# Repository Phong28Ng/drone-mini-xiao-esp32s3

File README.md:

# Drone mini XIAO ESP32-S3

Đồ án môn học của nhóm: drone mini 4 cánh dùng XIAO ESP32-S3, điều khiển bằng app ESP-Drone trên điện thoại qua Wi-Fi.

Drone đã bay thử được, giữ cân bằng khá ổn. Hiện tại con XIAO ESP32-S3 bị hỏng lúc tháo bo ra khỏi khung, nhóm đang chờ mạch mới về để lắp lại.

## Thư mục

- `firmware/` – code ESP-Drone, đã chỉnh chân cho bo của nhóm
- `hardware/` – file KiCad, Gerber, BOM, sơ đồ nguyên lý
- `frame/` – khung 3D
- `docs/` – sơ đồ khối, lưu đồ, ảnh app và ảnh drone

## Phần cứng

- XIAO ESP32-S3
- Cảm biến MPU-6050
- 4 motor coreless 6x15mm, mỗi motor 1 MOSFET KSI2300DS
- Pin LiPo 1S 3.7V
- PCB 4 lớp 17.75 x 21mm, làm lại từ thiết kế ESP-FLY rồi đặt xưởng gia công
- Khung tự vẽ trên SolidWorks rồi đem in 3D

Chân đang dùng:

| Chức năng | GPIO |
|---|---|
| Motor M1 (trước phải) | 7 |
| Motor M2 (sau phải) | 4 |
| Motor M3 (sau trái) | 3 |
| Motor M4 (trước trái) | 1 |
| SDA / SCL (MPU-6050) | 5 / 6 |
| INT (MPU-6050) | 8 |
| Đo điện áp pin | 2 |
| LED đỏ / LED xanh lá | 43 / 9 |

## Build và nạp code

Nhóm dùng ESP-IDF 5.0.

```
cd firmware
idf.py build
idf.py -p COMx flash monitor
```

Không chạy `idf.py set-target` vì nó sẽ tạo lại `sdkconfig` và mất cấu hình chân.

So với code gốc, nhóm sửa `sdkconfig` (chân motor, I2C, LED) và `motors.h` (cho motor quay thử lâu hơn lúc khởi động để dễ quan sát).

## Cách điều khiển

1. Cắm pin, đợi 4 motor quay thử lần lượt và LED xanh chớp 5 lần.
2. Điện thoại vào Wi-Fi `ESP-DRONE_xxxx`, mật khẩu `12345678`.
3. Mở app ESP-Drone, bấm kết nối, kéo ga về 0 trước rồi mới đẩy ga lên.

## Thành viên

- Ngô Hải Nam (nhóm trưởng) – thiết kế PCB, hàn mạch
- Phạm Chu Quốc – thiết kế và in khung 3D, cài app
- Nguyễn Hữu Phong – báo cáo, lưu đồ, tìm hiểu PID

GVHD: TS. Đỗ Trần Thắng – Trường Đại học Công nghệ, ĐHQGHN

## Tham khảo

- Firmware: [espressif/esp-drone](https://github.com/espressif/esp-drone)
- Mạch: [ESP-FLY](https://github.com/Seeed-Projects/Co-Create_ESP-FLY) của Max Imagination

Giấy phép GPL-3.0 theo dự án gốc.

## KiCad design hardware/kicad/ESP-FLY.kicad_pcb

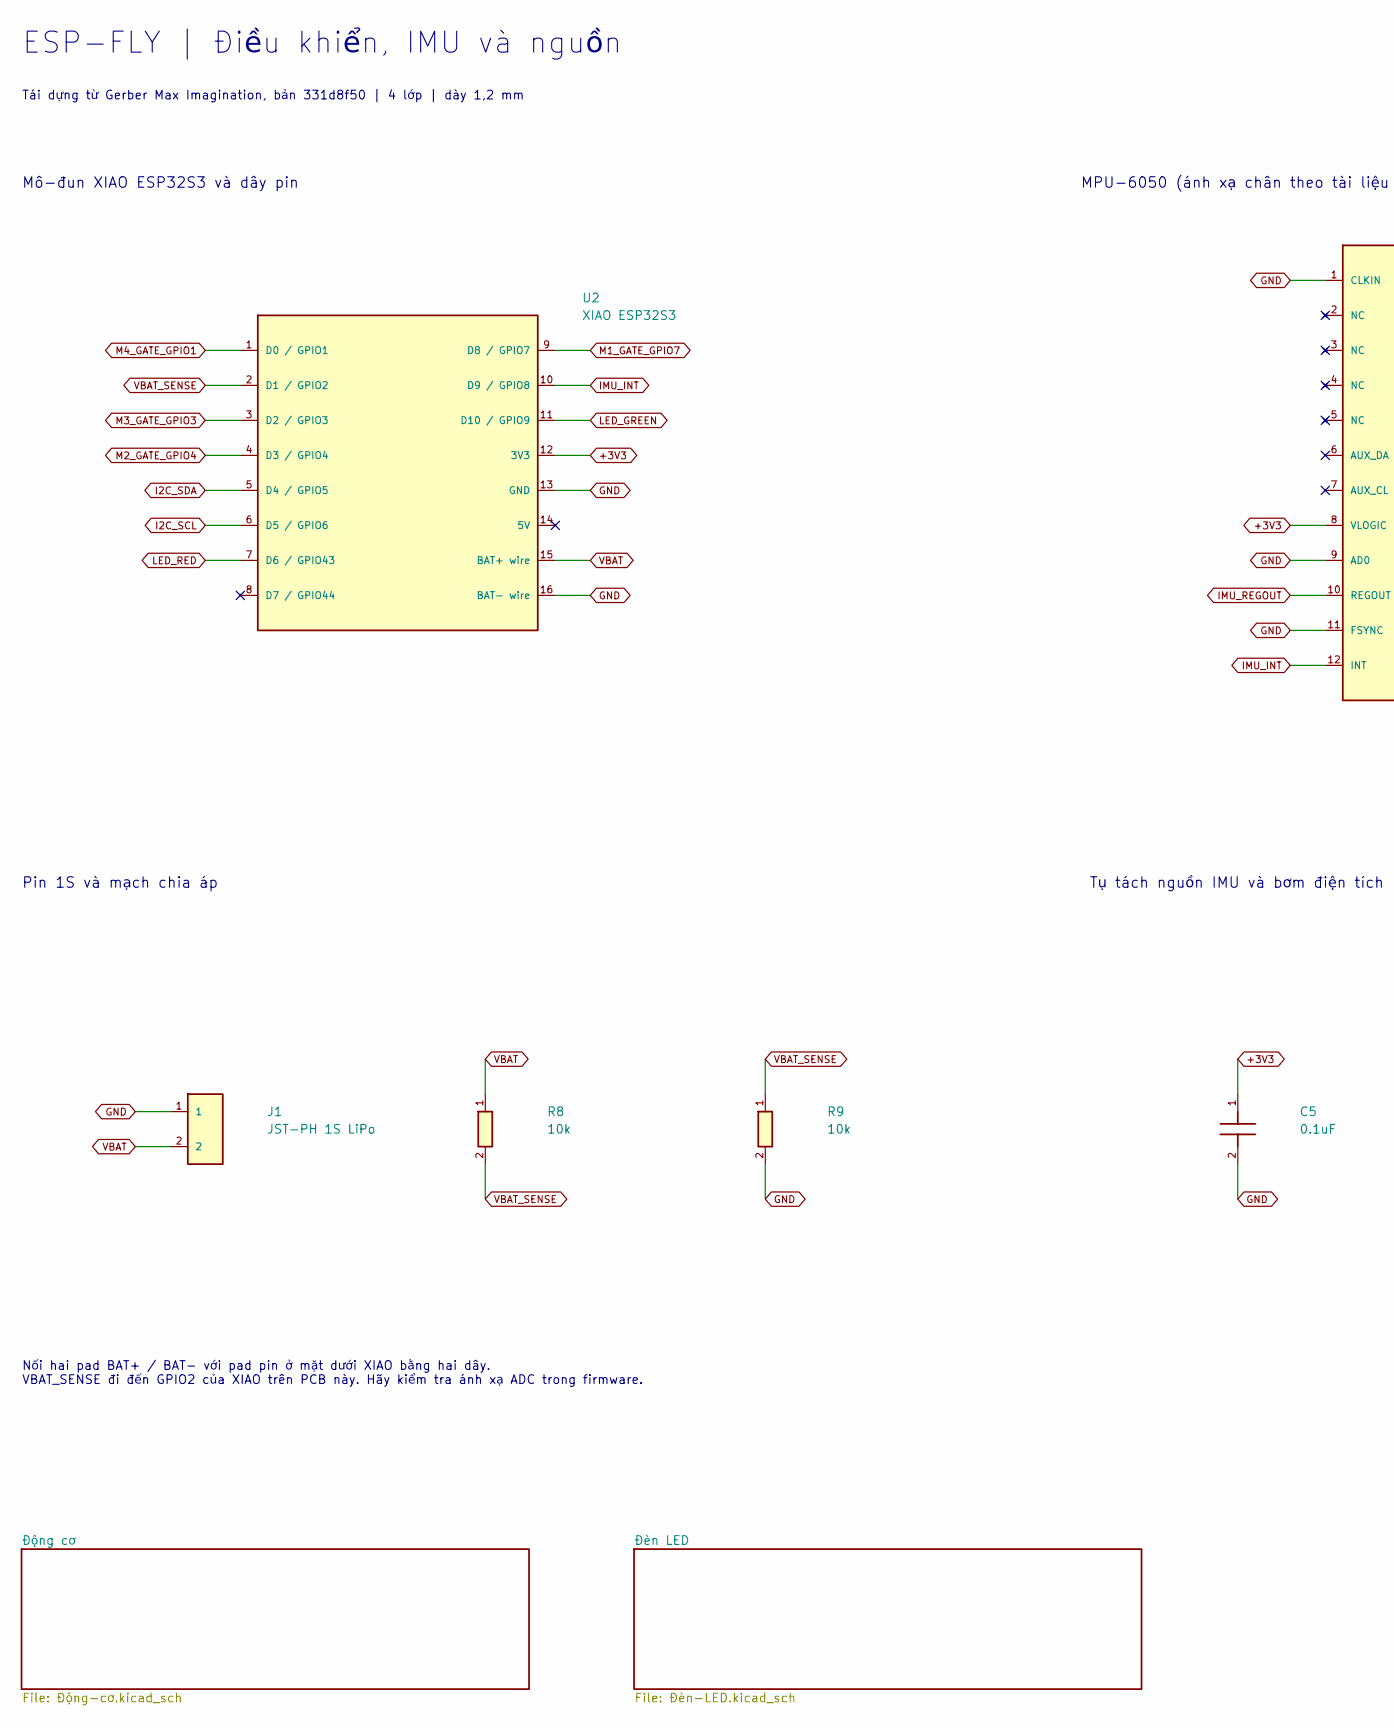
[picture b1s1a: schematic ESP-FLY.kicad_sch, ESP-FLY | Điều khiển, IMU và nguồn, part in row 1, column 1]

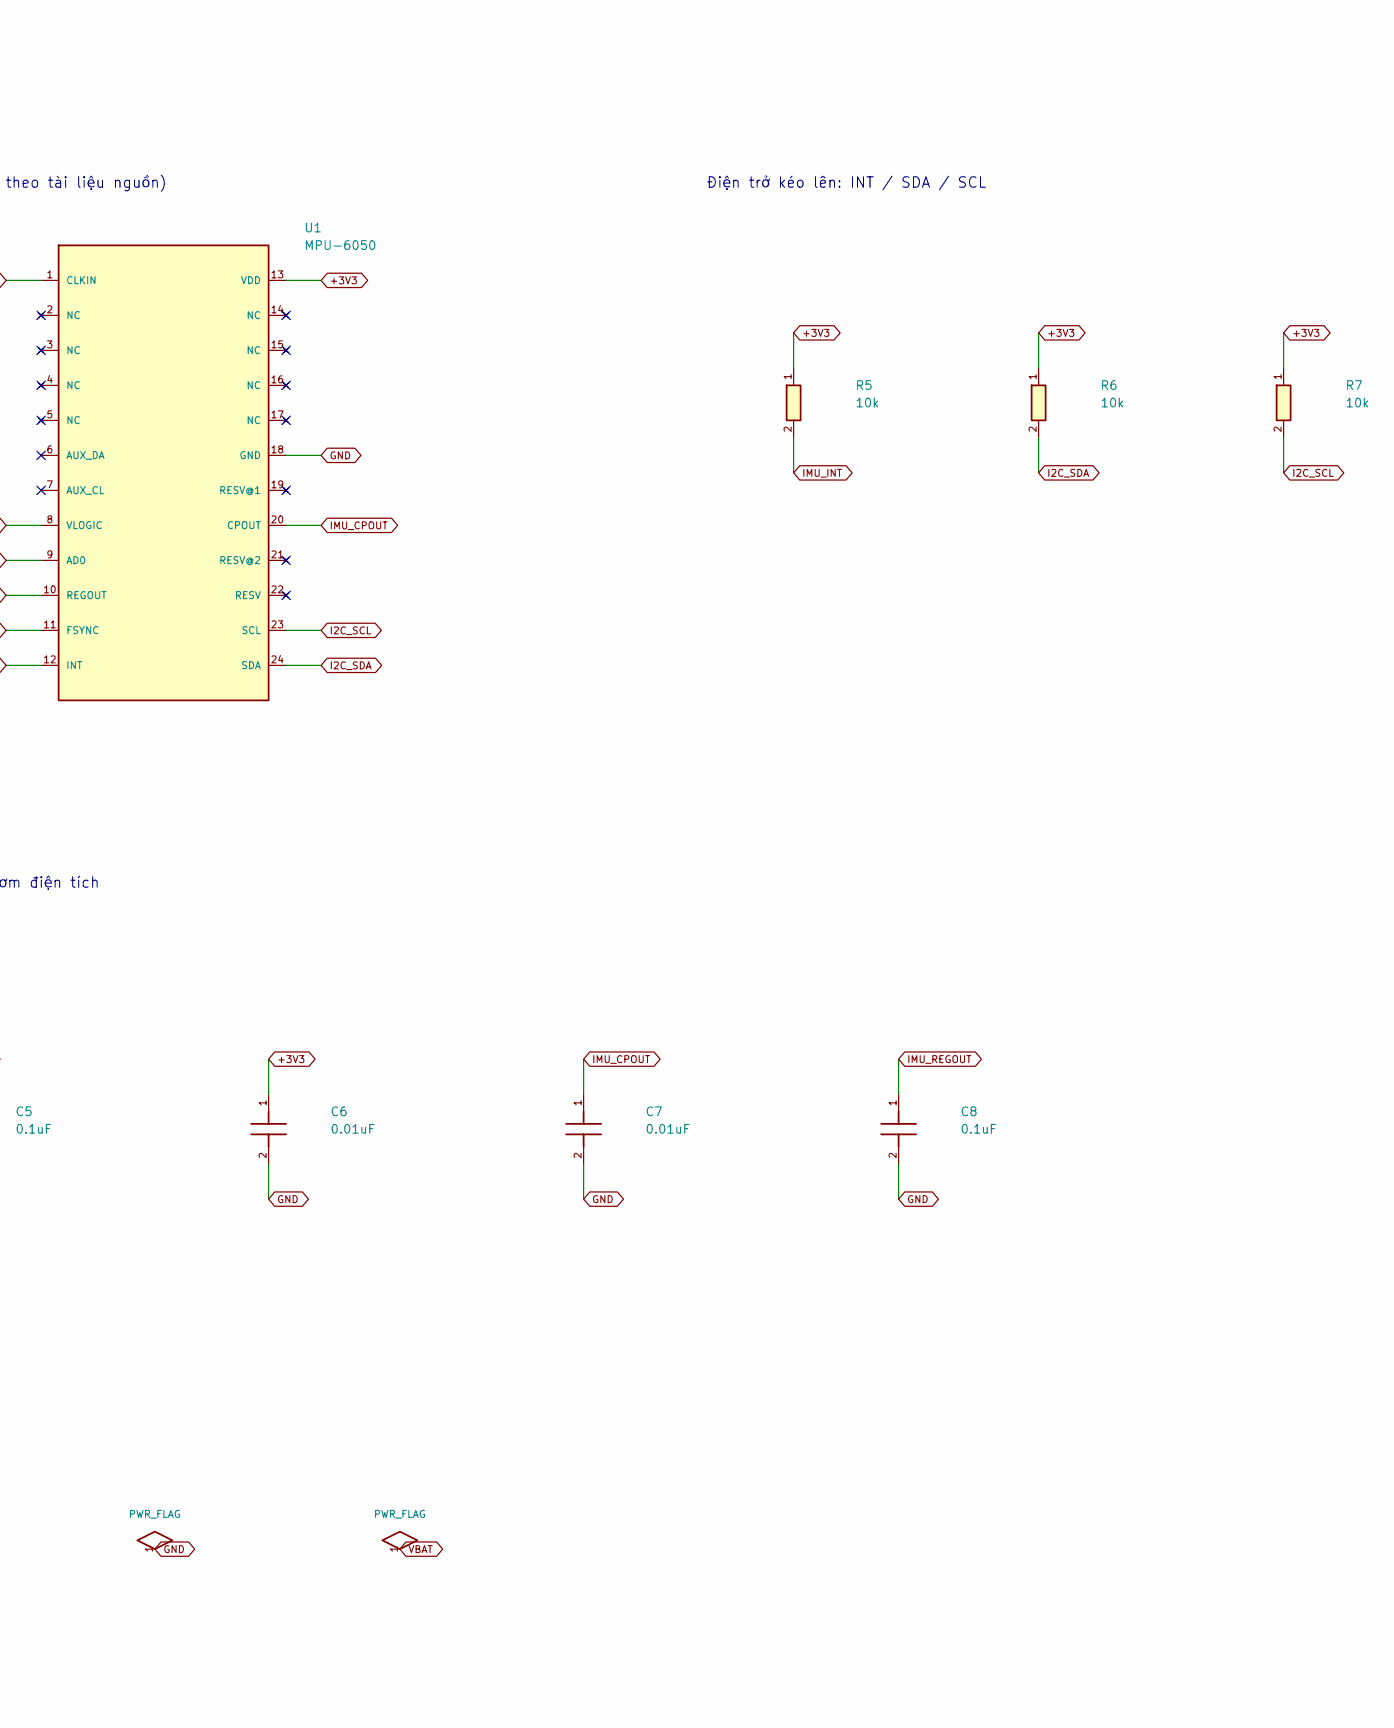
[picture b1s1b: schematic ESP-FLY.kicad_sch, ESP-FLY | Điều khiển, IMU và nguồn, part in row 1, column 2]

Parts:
C5: 0.1uF; C5; ManufacturerPartNumber CL21B104KBCNNNC
C6: 0.01uF; C6; ManufacturerPartNumber CC0805KRX7R9BB103
C7: 0.01uF; C7; ManufacturerPartNumber CC0805KRX7R9BB103
C8: 0.1uF; C8; ManufacturerPartNumber CL21B104KBCNNNC
J1: JST-PH 1S LiPo; J1; ManufacturerPartNumber S2B-PH-K-S(LF)(SN)
R5: 10k; R5; ManufacturerPartNumber FRC0805F1002TS
R6: 10k; R6; ManufacturerPartNumber FRC0805F1002TS
R7: 10k; R7; ManufacturerPartNumber FRC0805F1002TS
R8: 10k; R8; ManufacturerPartNumber FRC0805F1002TS
R9: 10k; R9; ManufacturerPartNumber FRC0805F1002TS
U1: MPU-6050; U1; ManufacturerPartNumber MPU-6050
U2: XIAO ESP32S3; U2

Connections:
+3V3: C5.1, C6.1, R5.1, R6.1, R7.1, U1.8 (VLOGIC), U1.13 (VDD), U2.12 (3V3); also elsewhere on the board
GND: C5.2, C6.2, C7.2, C8.2, J1.1, R9.2, U1.1 (CLKIN), U1.9 (AD0), U1.11 (FSYNC), U1.18 (GND), U2.13 (GND), U2.16 (BAT- wire); also elsewhere on the board
I2C_SCL: R7.2, U1.23 (SCL), U2.6 (D5 / GPIO6)
I2C_SDA: R6.2, U1.24 (SDA), U2.5 (D4 / GPIO5)
IMU_CPOUT: C7.1, U1.20 (CPOUT)
IMU_INT: R5.2, U1.12 (INT), U2.10 (D9 / GPIO8)
IMU_REGOUT: C8.1, U1.10 (REGOUT)
LED_GREEN: U2.11 (D10 / GPIO9); also elsewhere on the board
LED_RED: U2.7 (D6 / GPIO43); also elsewhere on the board
M1_GATE_GPIO7: U2.9 (D8 / GPIO7); also elsewhere on the board
M2_GATE_GPIO4: U2.4 (D3 / GPIO4); also elsewhere on the board
M3_GATE_GPIO3: U2.3 (D2 / GPIO3); also elsewhere on the board
M4_GATE_GPIO1: U2.1 (D0 / GPIO1); also elsewhere on the board
VBAT: J1.2, R8.1, U2.15 (BAT+ wire); also elsewhere on the board
VBAT_SENSE: R8.2, R9.1, U2.2 (D1 / GPIO2)

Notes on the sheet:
ESP-FLY | Điều khiển, IMU và nguồn
Tái dựng từ Gerber Max Imagination, bản 331d8f50 | 4 lớp | dày 1,2 mm
Mô-đun XIAO ESP32S3 và dây pin
MPU-6050 (ánh xạ chân theo tài liệu nguồn)
Điện trở kéo lên: INT / SDA / SCL
Pin 1S và mạch chia áp
Tụ tách nguồn IMU và bơm điện tích
Nối hai pad BAT+ / BAT- với pad pin ở mặt dưới XIAO bằng hai dây. VBAT_SENSE đi đến GPIO2 của XIAO trên PCB này. Hãy kiểm tra ánh xạ ADC trong firmware.

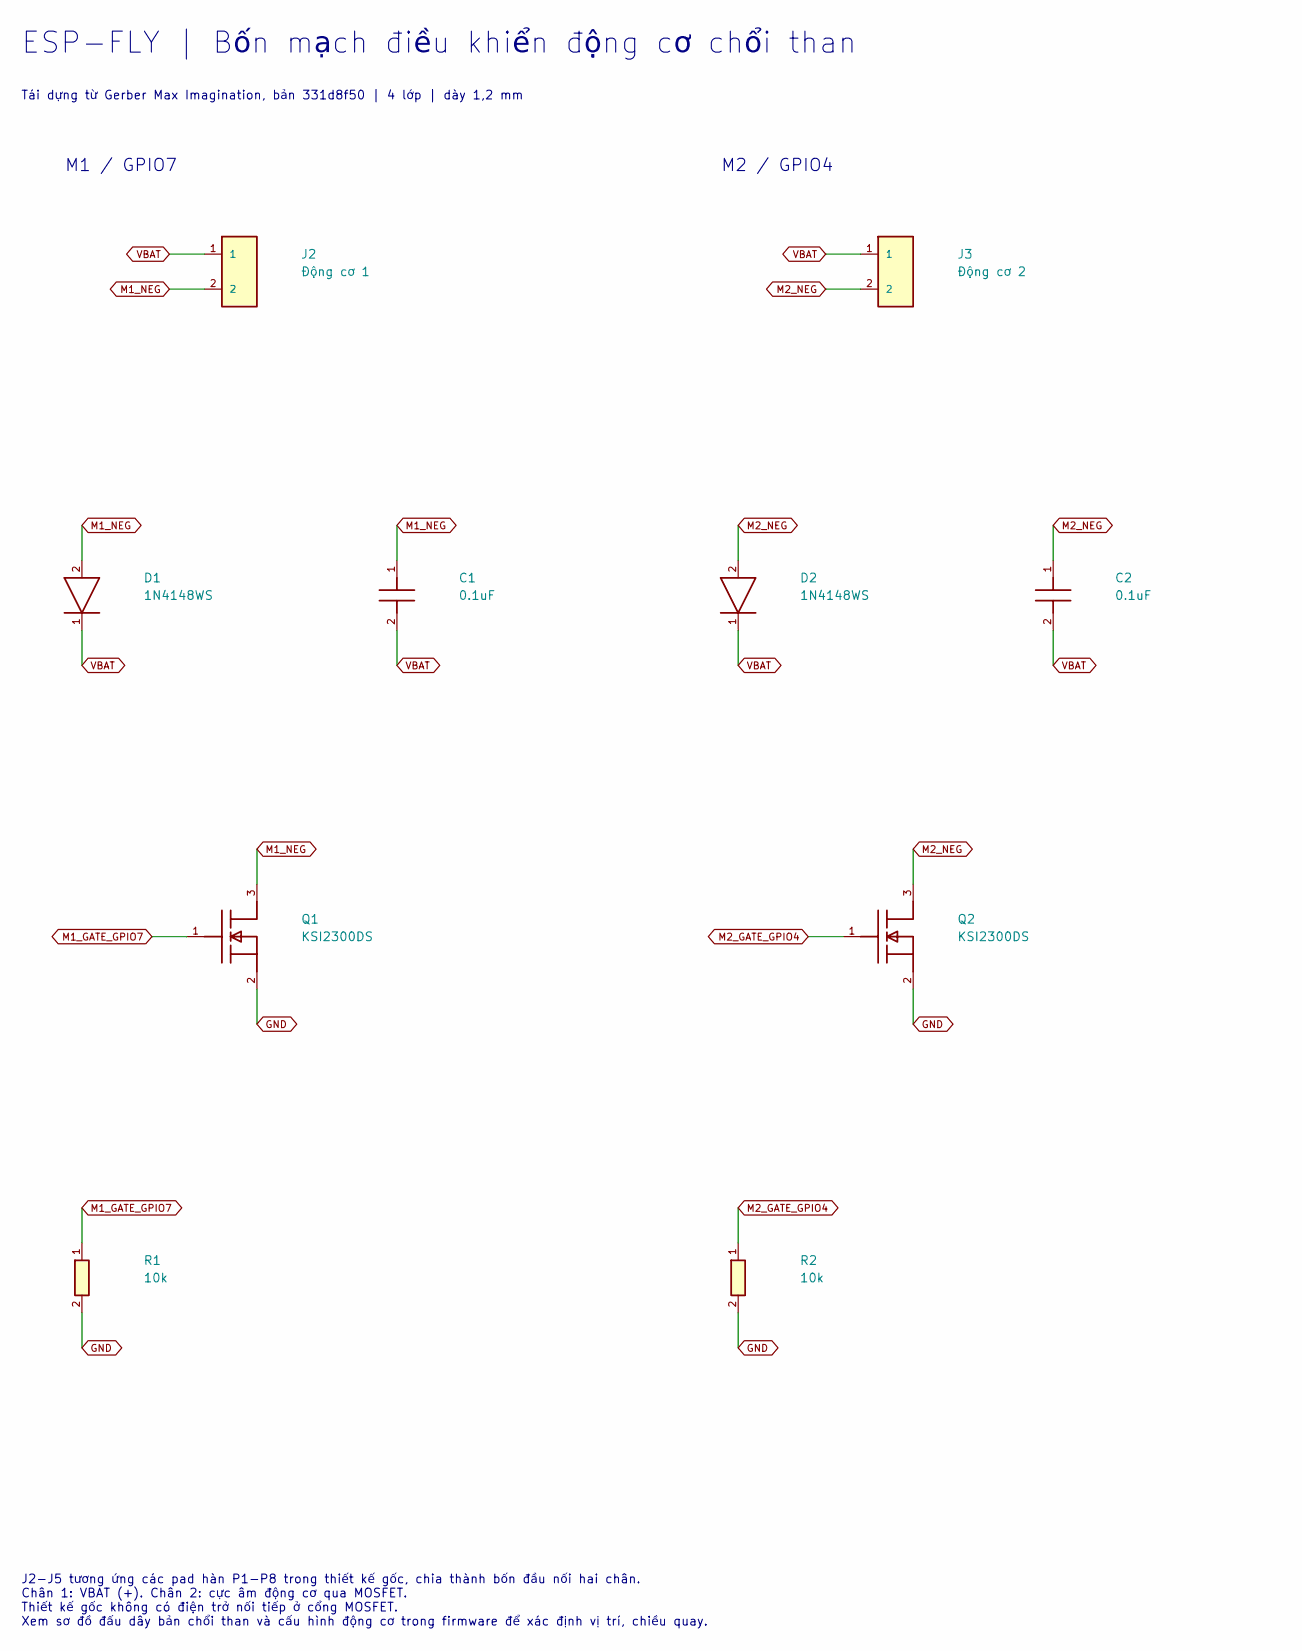
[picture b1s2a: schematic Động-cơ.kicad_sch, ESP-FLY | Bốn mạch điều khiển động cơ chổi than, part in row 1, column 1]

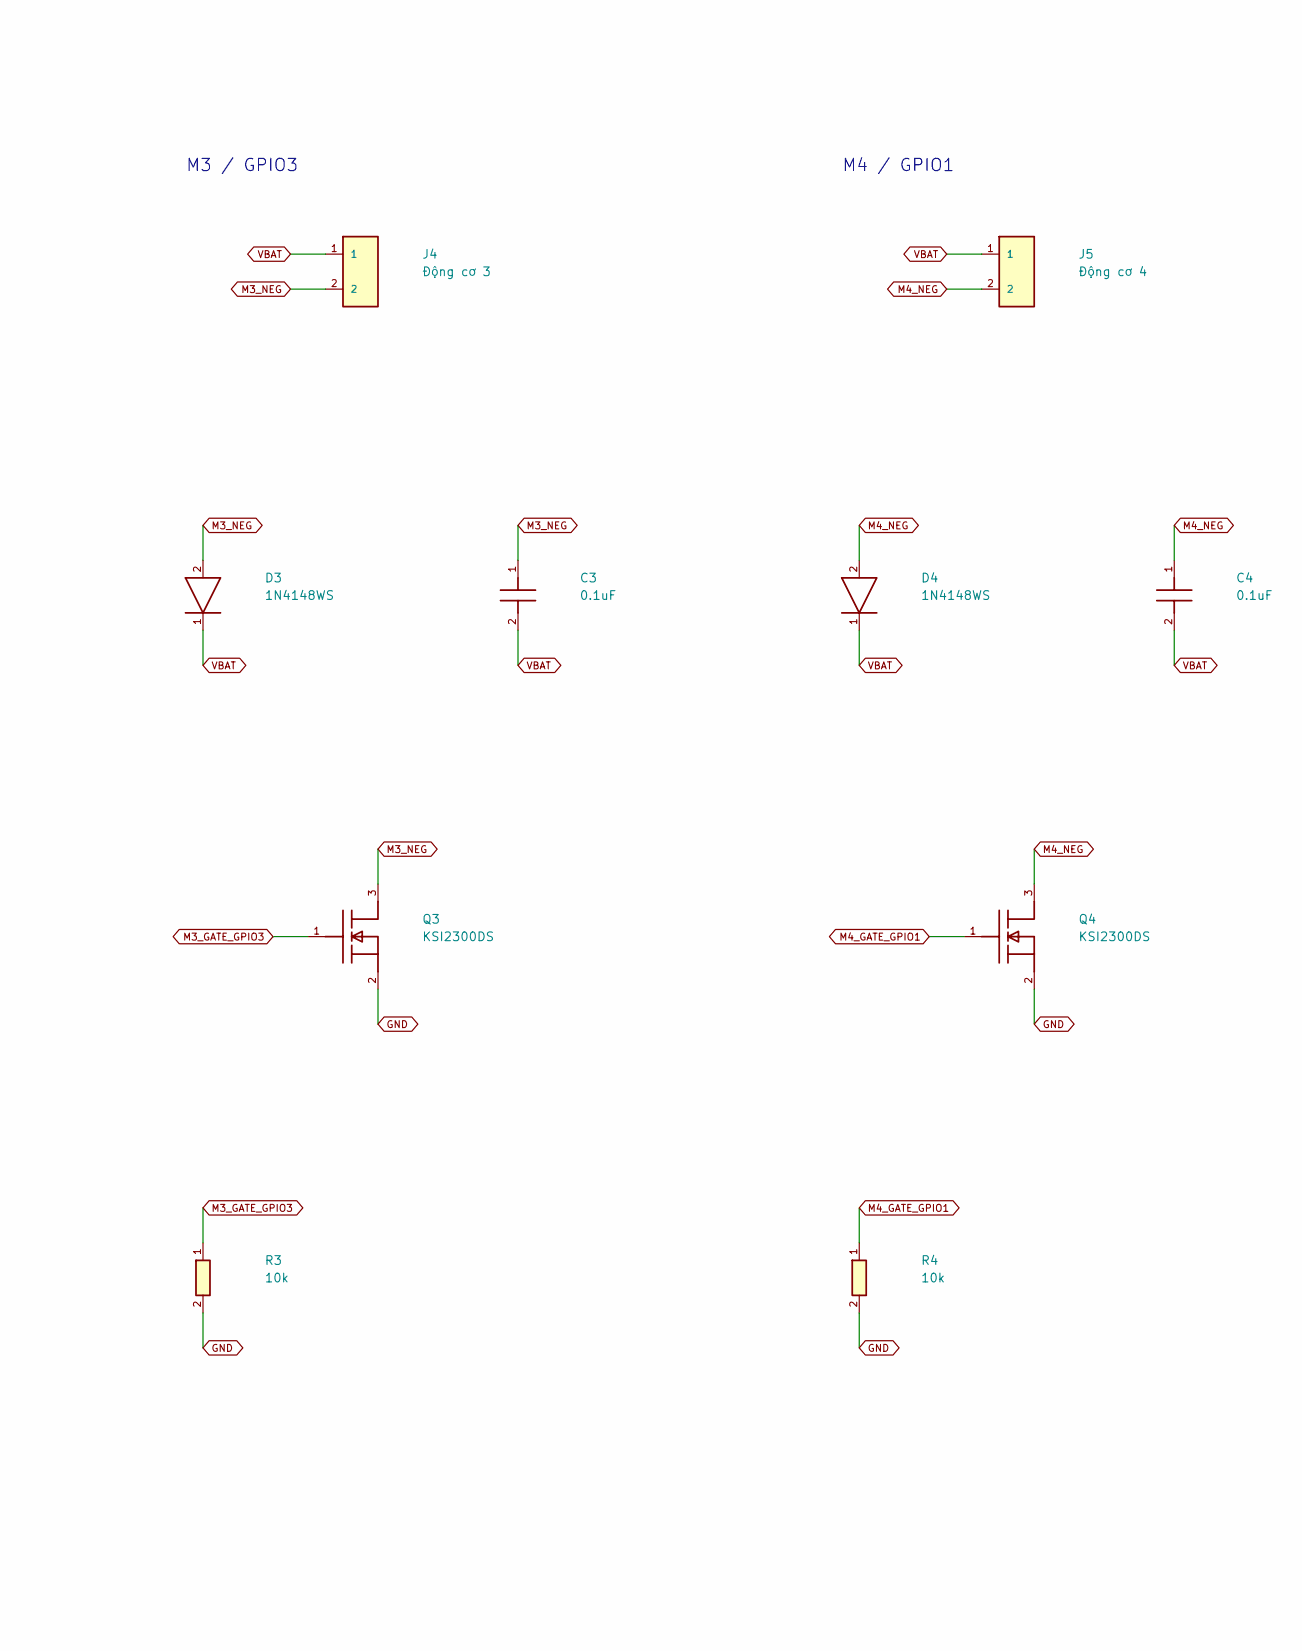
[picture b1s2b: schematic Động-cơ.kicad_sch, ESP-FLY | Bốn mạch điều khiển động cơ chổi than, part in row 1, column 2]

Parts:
C1: 0.1uF; C1; ManufacturerPartNumber CL21B104KBCNNNC
C2: 0.1uF; C2; ManufacturerPartNumber CL21B104KBCNNNC
C3: 0.1uF; C3; ManufacturerPartNumber CL21B104KBCNNNC
C4: 0.1uF; C4; ManufacturerPartNumber CL21B104KBCNNNC
D1: 1N4148WS; D1; ManufacturerPartNumber 1N4148WS-7-F
D2: 1N4148WS; D2; ManufacturerPartNumber 1N4148WS-7-F
D3: 1N4148WS; D3; ManufacturerPartNumber 1N4148WS-7-F
D4: 1N4148WS; D4; ManufacturerPartNumber 1N4148WS-7-F
J2: Động cơ 1; J2
J3: Động cơ 2; J3
J4: Động cơ 3; J4
J5: Động cơ 4; J5
Q1: KSI2300DS; Q1; ManufacturerPartNumber KSI2300DS-T1-GE3
Q2: KSI2300DS; Q2; ManufacturerPartNumber KSI2300DS-T1-GE3
Q3: KSI2300DS; Q3; ManufacturerPartNumber KSI2300DS-T1-GE3
Q4: KSI2300DS; Q4; ManufacturerPartNumber KSI2300DS-T1-GE3
R1: 10k; R1; ManufacturerPartNumber FRC0805F1002TS
R2: 10k; R2; ManufacturerPartNumber FRC0805F1002TS
R3: 10k; R3; ManufacturerPartNumber FRC0805F1002TS
R4: 10k; R4; ManufacturerPartNumber FRC0805F1002TS

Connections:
GND: Q1.2 (S), Q2.2 (S), Q3.2 (S), Q4.2 (S), R1.2, R2.2, R3.2, R4.2; also elsewhere on the board
M1_GATE_GPIO7: Q1.1 (G), R1.1; also elsewhere on the board
M1_NEG: C1.1, D1.2 (A), J2.2, Q1.3 (D)
M2_GATE_GPIO4: Q2.1 (G), R2.1; also elsewhere on the board
M2_NEG: C2.1, D2.2 (A), J3.2, Q2.3 (D)
M3_GATE_GPIO3: Q3.1 (G), R3.1; also elsewhere on the board
M3_NEG: C3.1, D3.2 (A), J4.2, Q3.3 (D)
M4_GATE_GPIO1: Q4.1 (G), R4.1; also elsewhere on the board
M4_NEG: C4.1, D4.2 (A), J5.2, Q4.3 (D)
VBAT: C1.2, C2.2, C3.2, C4.2, D1.1 (K), D2.1 (K), D3.1 (K), D4.1 (K), J2.1, J3.1, J4.1, J5.1; also elsewhere on the board

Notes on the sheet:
ESP-FLY | Bốn mạch điều khiển động cơ chổi than
Tái dựng từ Gerber Max Imagination, bản 331d8f50 | 4 lớp | dày 1,2 mm
M1 / GPIO7
M2 / GPIO4
M3 / GPIO3
M4 / GPIO1
J2-J5 tương ứng các pad hàn P1-P8 trong thiết kế gốc, chia thành bốn đầu nối hai chân. Chân 1: VBAT (+). Chân 2: cực âm động cơ qua MOSFET. Thiết kế gốc không có điện trở nối tiếp ở cổng MOSFET. Xem sơ đồ đấu dây bản chổi than và cấu hình động cơ trong firmware để xác định vị trí, chiều quay.

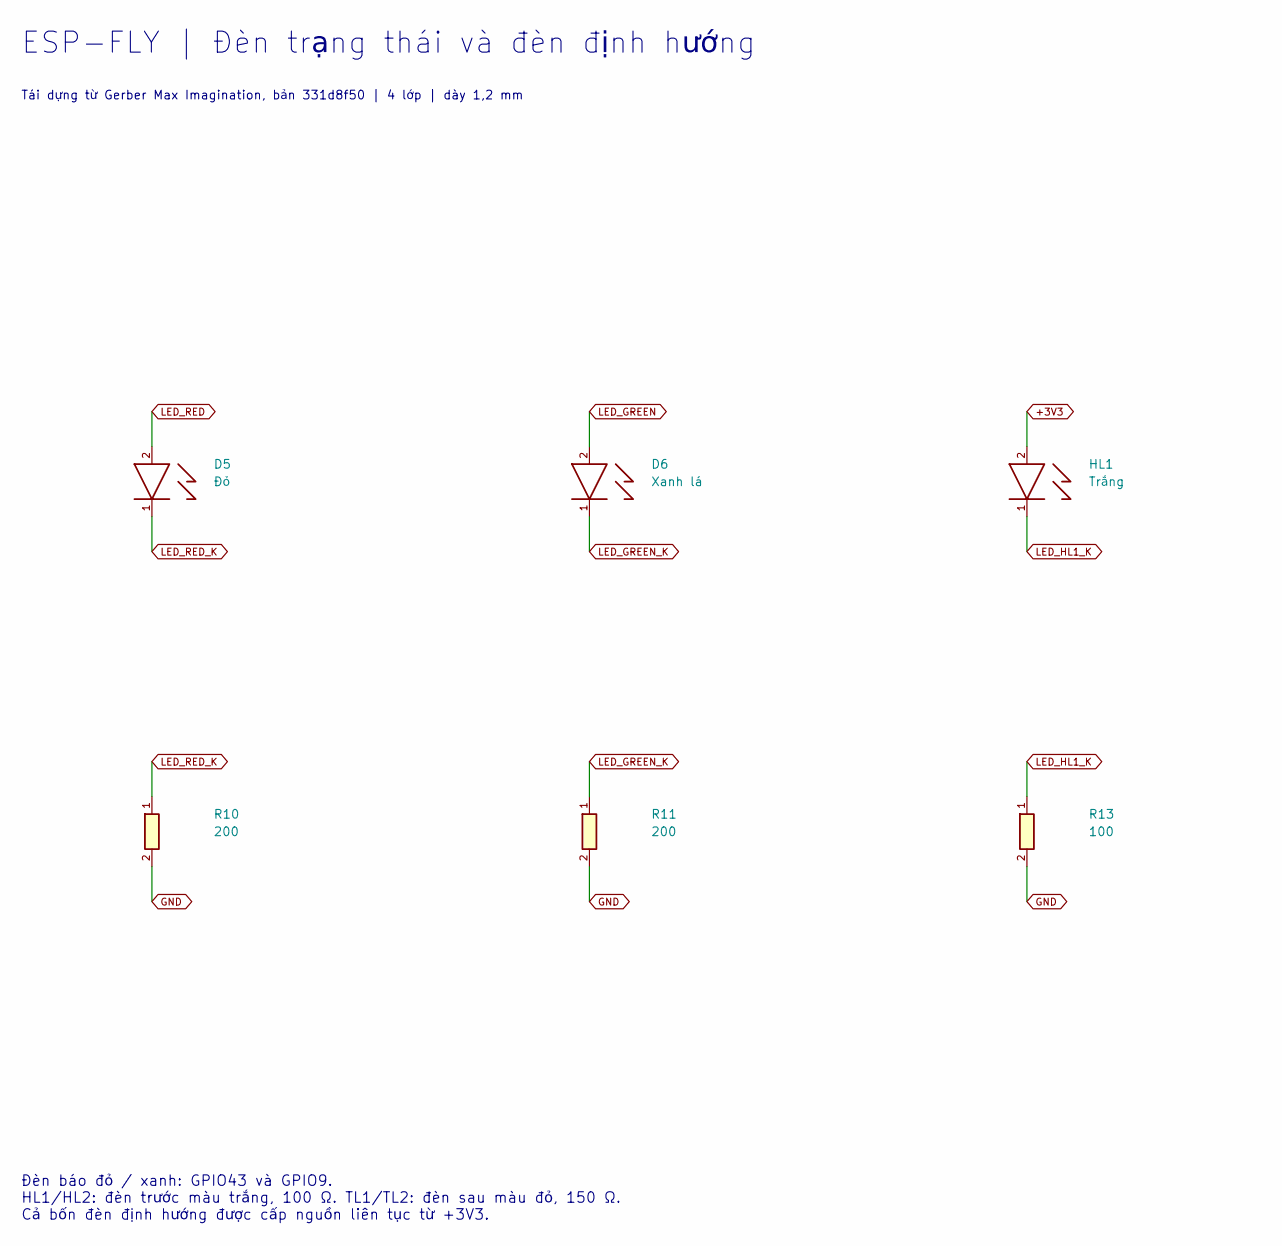
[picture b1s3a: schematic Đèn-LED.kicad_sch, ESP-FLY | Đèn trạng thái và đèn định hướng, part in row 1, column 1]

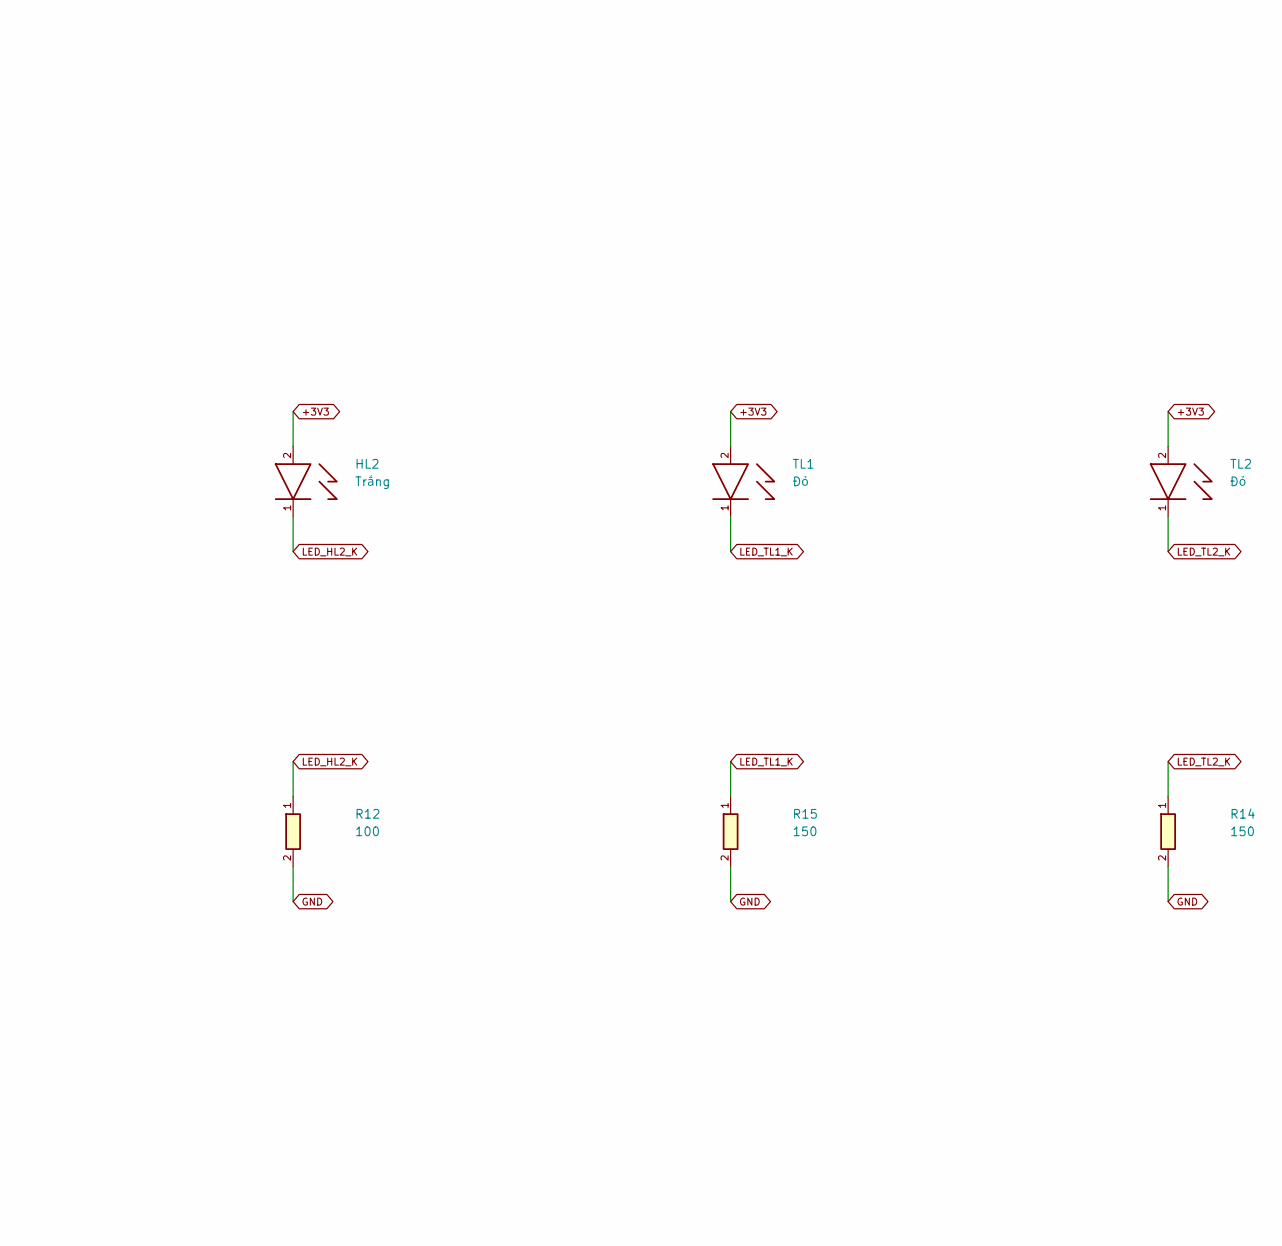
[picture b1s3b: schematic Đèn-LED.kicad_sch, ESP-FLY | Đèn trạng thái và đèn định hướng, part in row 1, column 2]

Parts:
D5: Đỏ; D5; ManufacturerPartNumber TZ-P2-0805RTCS2-0.8T
D6: Xanh lá; D6; ManufacturerPartNumber ORH-G35A
HL1: Trắng; HL1; ManufacturerPartNumber TZ-P2-0805WYCS2-0.8T
HL2: Trắng; HL2; ManufacturerPartNumber TZ-P2-0805WYCS2-0.8T
R10: 200; R10; ManufacturerPartNumber 0805W8F2000T5E
R11: 200; R11; ManufacturerPartNumber 0805W8F2000T5E
R12: 100; R12; ManufacturerPartNumber CRCW0805100RFKEA
R13: 100; R13; ManufacturerPartNumber CRCW0805100RFKEA
R14: 150; R14; ManufacturerPartNumber RMS10FT1500
R15: 150; R15; ManufacturerPartNumber RMS10FT1500
TL1: Đỏ; TL1; ManufacturerPartNumber TZ-P2-0805RTCS2-0.8T
TL2: Đỏ; TL2; ManufacturerPartNumber TZ-P2-0805RTCS2-0.8T

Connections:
+3V3: HL1.2 (A), HL2.2 (A), TL1.2 (A), TL2.2 (A); also elsewhere on the board
GND: R10.2, R11.2, R12.2, R13.2, R14.2, R15.2; also elsewhere on the board
LED_GREEN: D6.2 (A); also elsewhere on the board
LED_GREEN_K: D6.1 (K), R11.1
LED_HL1_K: HL1.1 (K), R13.1
LED_HL2_K: HL2.1 (K), R12.1
LED_RED: D5.2 (A); also elsewhere on the board
LED_RED_K: D5.1 (K), R10.1
LED_TL1_K: R15.1, TL1.1 (K)
LED_TL2_K: R14.1, TL2.1 (K)

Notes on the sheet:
ESP-FLY | Đèn trạng thái và đèn định hướng
Tái dựng từ Gerber Max Imagination, bản 331d8f50 | 4 lớp | dày 1,2 mm
Đèn báo đỏ / xanh: GPIO43 và GPIO9. HL1/HL2: đèn trước màu trắng, 100 Ω. TL1/TL2: đèn sau màu đỏ, 150 Ω. Cả bốn đèn định hướng được cấp nguồn liên tục từ +3V3.

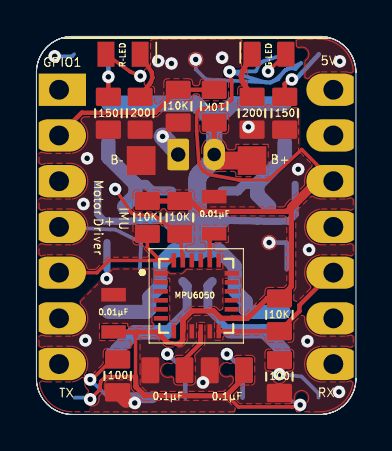
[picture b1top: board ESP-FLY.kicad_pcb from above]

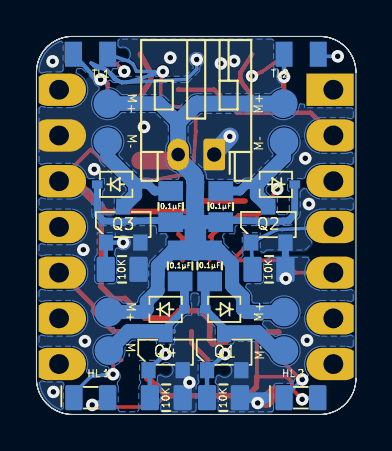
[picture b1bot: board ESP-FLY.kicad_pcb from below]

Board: 4 copper layers, 17.8 x 21.0 mm, 44 parts (25 on the bottom side), 25 nets.

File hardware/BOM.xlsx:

Ký hiệu tham chiếu | Số lượng | Giá trị / mô tả | Dấu chân PCB (Footprint) | Mã nhà sản xuất (MPN) | Công nghệ lắp ráp
R10, R11 | 2 | 200 | 0805 (2012 metric) | 0805W8F2000T5E | SMT
D1, D2, D3, D4 | 4 | 1N4148WS | SOD-323 | 1N4148WS-7-F | SMT
C6, C7 | 2 | 0.01uF | 0805 (2012 metric) | CC0805KRX7R9BB103 | SMT
C1, C2, C3, C4, C5, C8 | 6 | 0.1uF | 0805 (2012 metric) | CL21B104KBCNNNC | SMT
R12, R13 | 2 | 100 | 0805 (2012 metric) | CRCW0805100RFKEA | SMT
R1, R2, R3, R4, R5, R6, R7, R8, R9 | 9 | 10k | 0805 (2012 metric) | FRC0805F1002TS | SMT
Q1, Q2, Q3, Q4 | 4 | KSI2300DS | SOT-23 | KSI2300DS-T1-GE3 | SMT
U1 | 1 | MPU-6050 | QFN-24 4x4mm P0.5mm | MPU-6050 | SMT
D6 | 1 | Xanh lá | 0805 (2012 metric) | ORH-G35A | SMT
R14, R15 | 2 | 150 | 0805 (2012 metric) | RMS10FT1500 | SMT
J1 | 1 | JST-PH 1S LiPo | JST-PH 2pin P2.00mm right-angle THT | S2B-PH-K-S(LF)(SN) | THT
D5, TL1, TL2 | 3 | Đỏ | 0805 (2012 metric) | TZ-P2-0805RTCS2-0.8T | SMT
HL1, HL2 | 2 | Trắng | 0805 (2012 metric) | TZ-P2-0805WYCS2-0.8T | SMT
Tổng cộng | 39
